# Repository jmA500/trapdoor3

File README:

This project describes a 1.8MB/2MB Trapdoor expansion for the Amiga
500. It includes the Schematics and PCB in the Autodesk Eagle format.

For a detailed description of the project including a comprehensive
Theory of operation, refert to:

https://www.jm27.de/amiga-500-trapdoor-extension/

All the files are licensed under the GPLv2, please mention
jmA500@metweb.de as the original author.

Acknowlegements go to Paradroid at the a1k.org/forum and Individual
Computers for useful suggestions.

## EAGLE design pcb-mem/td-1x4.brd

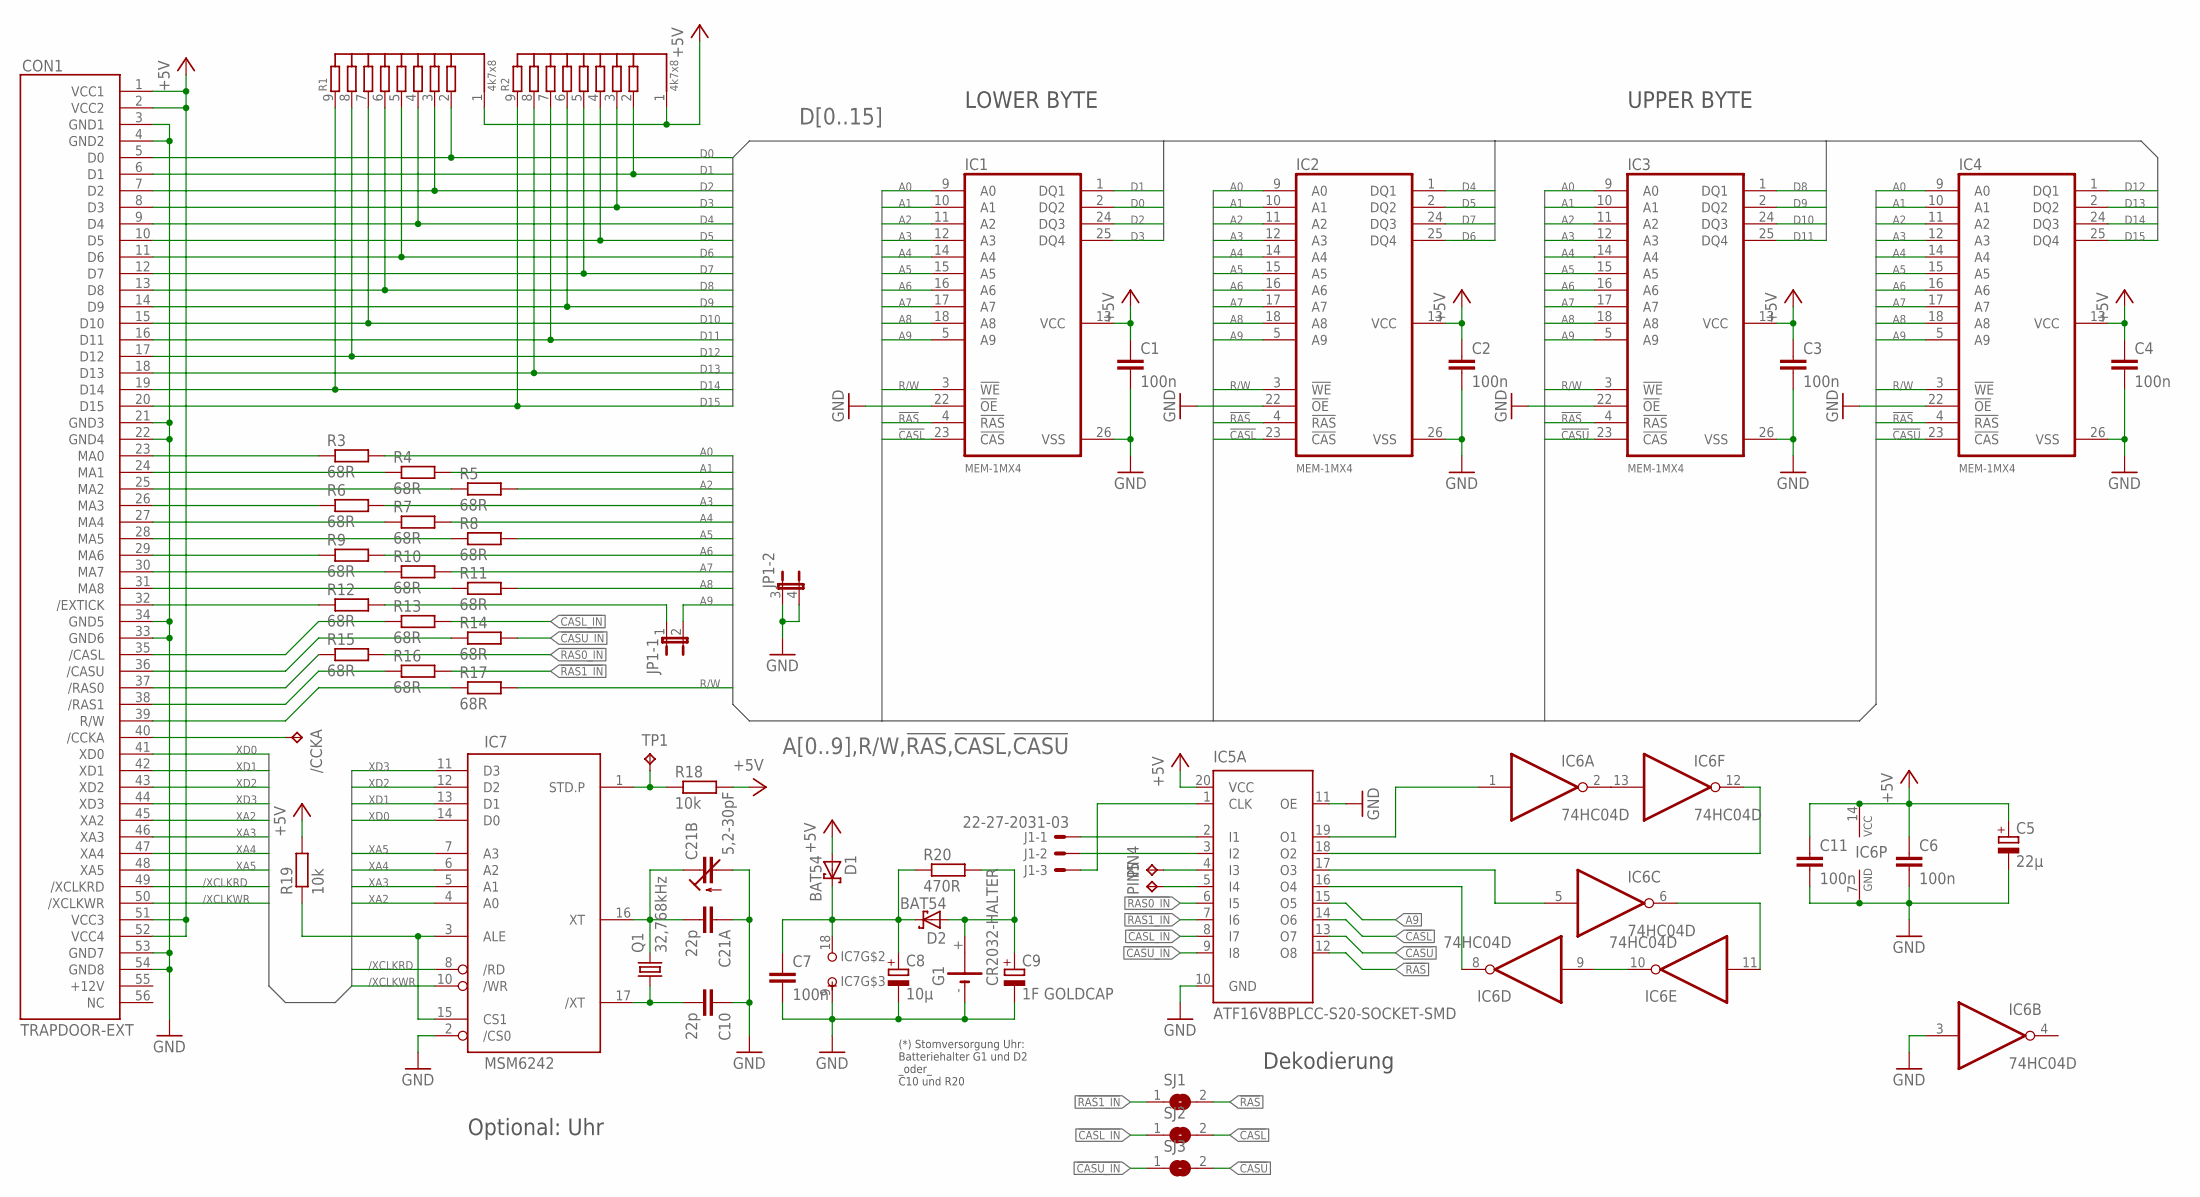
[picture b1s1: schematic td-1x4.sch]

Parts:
/CCKA: PIN2; B1,27
C1, C2, C3, C4, C6, C7, C11: 100n; C0805
C5: 22µ; SMC_C
C8: 10µ; SMC_A
C9: 1F GOLDCAP; GOLDCAP-5
C10, C21A: 22p; C0805
C21B: 5,2-30pF; CTRIM3050.504
CON1: TRAPDOOR-EXT; 2X28/90
D1, D2: BAT54; SOT23
G1: CR2032-HALTER; HALTER2032
IC1, IC2, IC3, IC4: MEM-1MX4; SOJ26-20
IC5A: ATF16V8BPLCC-S20-SOCKET-SMD; PLCC-S20-SOCKET-SMD
IC6: 74HC04D; SO14
IC7: MSM6242; DIL18
J1: 22-27-2031-03; 6410-03
JP1: JP2QE; JP2Q
PIN4: PIN4; B1,27
PIN5: PIN5; B1,27
Q1: 32,768kHz; TC26V
R1, R2: 4k7x8; RN-9
R3, R4, R5, R6, R7, R8, R9, R10, R11, R12, R13, R14, R15, R16, R17: 68R; R0805
R18, R19: 10k; R0805
R20: 470R; R0805
SJ1, SJ2, SJ3: SJ
TP1: TPB1,27; B1,27

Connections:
!CASL: IC1.23 (!CAS), IC2.23 (!CAS), IC5A.14 (O6), SJ2.2
!CASL_IN: IC5A.8 (I7), R13.2, SJ2.1
!CASU: IC3.23 (!CAS), IC4.23 (!CAS), IC5A.13 (O7), SJ3.2
!CASU_IN: IC5A.9 (I8), R14.2, SJ3.1
!EXRAM: CON1.32 (/EXTICK), R12.1
!RAS: IC1.4 (!RAS), IC2.4 (!RAS), IC3.4 (!RAS), IC4.4 (!RAS), IC5A.12 (O8), SJ1.2
!RAS0_IN: IC5A.6 (I5), R15.2
!RAS1_IN: IC5A.7 (I6), R16.2, SJ1.1
+5V: C1.1, C2.1, C3.1, C4.1, C5.+, C6.1, C11.1, CON1.1 (VCC1), CON1.2 (VCC2), CON1.51 (VCC3), CON1.52 (VCC4), D1.1 (A), IC1.13 (VCC), IC2.13 (VCC), IC3.13 (VCC), IC4.13 (VCC), IC5A.20 (VCC), IC6.14 (VCC), R1.1, R2.1, R18.2, R19.2
/XCLKRD: CON1.49 (/XCLKRD), IC7.8 (/RD)
/XCLKWR: CON1.50 (/XCLKWR), IC7.10 (/WR)
A0: IC1.9 (A0), IC2.9 (A0), IC3.9 (A0), IC4.9 (A0), R3.2
A1: IC1.10 (A1), IC2.10 (A1), IC3.10 (A1), IC4.10 (A1), R4.2
A2: IC1.11 (A2), IC2.11 (A2), IC3.11 (A2), IC4.11 (A2), R5.2
A3: IC1.12 (A3), IC2.12 (A3), IC3.12 (A3), IC4.12 (A3), R6.2
A4: IC1.14 (A4), IC2.14 (A4), IC3.14 (A4), IC4.14 (A4), R7.2
A5: IC1.15 (A5), IC2.15 (A5), IC3.15 (A5), IC4.15 (A5), R8.2
A6: IC1.16 (A6), IC2.16 (A6), IC3.16 (A6), IC4.16 (A6), R9.2
A7: IC1.17 (A7), IC2.17 (A7), IC3.17 (A7), IC4.17 (A7), R10.2
A8: IC1.18 (A8), IC2.18 (A8), IC3.18 (A8), IC4.18 (A8), R11.2
A9: IC1.5 (A9), IC2.5 (A9), IC3.5 (A9), IC4.5 (A9), IC5A.15 (O5), JP1.2
D0: CON1.5 (D0), IC1.2 (DQ2), R1.2
D1: CON1.6 (D1), IC1.1 (DQ1), R2.2
D2: CON1.7 (D2), IC1.24 (DQ3), R1.3
D3: CON1.8 (D3), IC1.25 (DQ4), R2.3
D4: CON1.9 (D4), IC2.1 (DQ1), R1.4
D5: CON1.10 (D5), IC2.2 (DQ2), R2.4
D6: CON1.11 (D6), IC2.25 (DQ4), R1.5
D7: CON1.12 (D7), IC2.24 (DQ3), R2.5
D8: CON1.13 (D8), IC3.1 (DQ1), R1.6
D9: CON1.14 (D9), IC3.2 (DQ2), R2.6
D10: CON1.15 (D10), IC3.24 (DQ3), R1.7
D11: CON1.16 (D11), IC3.25 (DQ4), R2.7
D12: CON1.17 (D12), IC4.1 (DQ1), R1.8
D13: CON1.18 (D13), IC4.2 (DQ2), R2.8
D14: CON1.19 (D14), IC4.24 (DQ3), R1.9
D15: CON1.20 (D15), IC4.25 (DQ4), R2.9
GND: C1.2, C2.2, C3.2, C4.2, C5.-, C6.2, C7.2, C8.-, C9.-, C10.1, C11.2, C21A.1, C21B.2 (A), CON1.3 (GND1), CON1.4 (GND2), CON1.21 (GND3), CON1.22 (GND4), CON1.33 (GND6), CON1.34 (GND5), CON1.53 (GND7), CON1.54 (GND8), G1.-, IC1.22 (!OE), IC1.26 (VSS), IC2.22 (!OE), IC2.26 (VSS), IC3.22 (!OE), IC3.26 (VSS), IC4.22 (!OE), IC4.26 (VSS), IC5A.10 (GND), IC5A.11 (OE), IC6.3 (I), IC6.7 (GND), IC7.2 (/CS0), IC7.9 (-UB), JP1.3 (1), JP1.4 (2)
unnamed: CON1.23 (MA0), R3.1
unnamed: CON1.24 (MA1), R4.1
unnamed: CON1.25 (MA2), R5.1
unnamed: CON1.26 (MA3), R6.1
unnamed: CON1.28 (MA5), R8.1
unnamed: CON1.27 (MA4), R7.1
unnamed: CON1.38 (/RAS1), R16.1
unnamed: CON1.29 (MA6), R9.1
unnamed: CON1.30 (MA7), R10.1
unnamed: CON1.31 (MA8), R11.1
unnamed: CON1.35 (/CASL), R13.1
unnamed: CON1.36 (/CASU), R14.1
unnamed: IC5A.18 (O2), IC6.12 (O)
unnamed: CON1.39 (R/W), R17.1
unnamed: C21A.2, C21B.1 (E), IC7.16 (XT), Q1.2
unnamed: C10.2, IC7.17 (/XT), Q1.1
unnamed: IC7.3 (ALE), IC7.15 (CS1), R19.1
unnamed: IC5A.3 (I2), J1.2
unnamed: IC7.1 (STD.P), R18.1, TP1.TP
unnamed: C9.+, D2.1 (A), G1.+, R20.2
unnamed: C7.1, C8.+, D1.3 (C), D2.3 (C), IC7.18 (+UB), R20.1
unnamed: IC5A.4 (I3), PIN4.TP
unnamed: IC5A.5 (I4), PIN5.TP
unnamed: IC6.9 (I), IC6.10 (O)
unnamed: IC5A.16 (O4), IC6.8 (O)
unnamed: IC5A.17 (O3), IC6.5 (I)
unnamed: CON1.37 (/RAS0), R15.1
unnamed: IC6.2 (O), IC6.13 (I)
unnamed: IC5A.19 (O1), IC6.1 (I)
unnamed: IC5A.1 (CLK), J1.3
unnamed: IC6.6 (O), IC6.11 (I)
unnamed: IC5A.2 (I1), J1.1
unnamed: /CCKA.TP, CON1.40 (/CCKA)
unnamed: JP1.1, R12.2
R/W: IC1.3 (!WE), IC2.3 (!WE), IC3.3 (!WE), IC4.3 (!WE), R17.2
XA2: CON1.45 (XA2), IC7.4 (A0)
XA3: CON1.46 (XA3), IC7.5 (A1)
XA4: CON1.47 (XA4), IC7.6 (A2)
XA5: CON1.48 (XA5), IC7.7 (A3)
XD0: CON1.41 (XD0), IC7.14 (D0)
XD1: CON1.42 (XD1), IC7.13 (D1)
XD2: CON1.43 (XD2), IC7.12 (D2)
XD3: CON1.44 (XD3), IC7.11 (D3)

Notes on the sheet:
LOWER BYTE
UPPER BYTE
Optional: Uhr
Dekodierung
(*) Stomversorgung Uhr: Batteriehalter G1 und D2 _oder_ C10 und R20

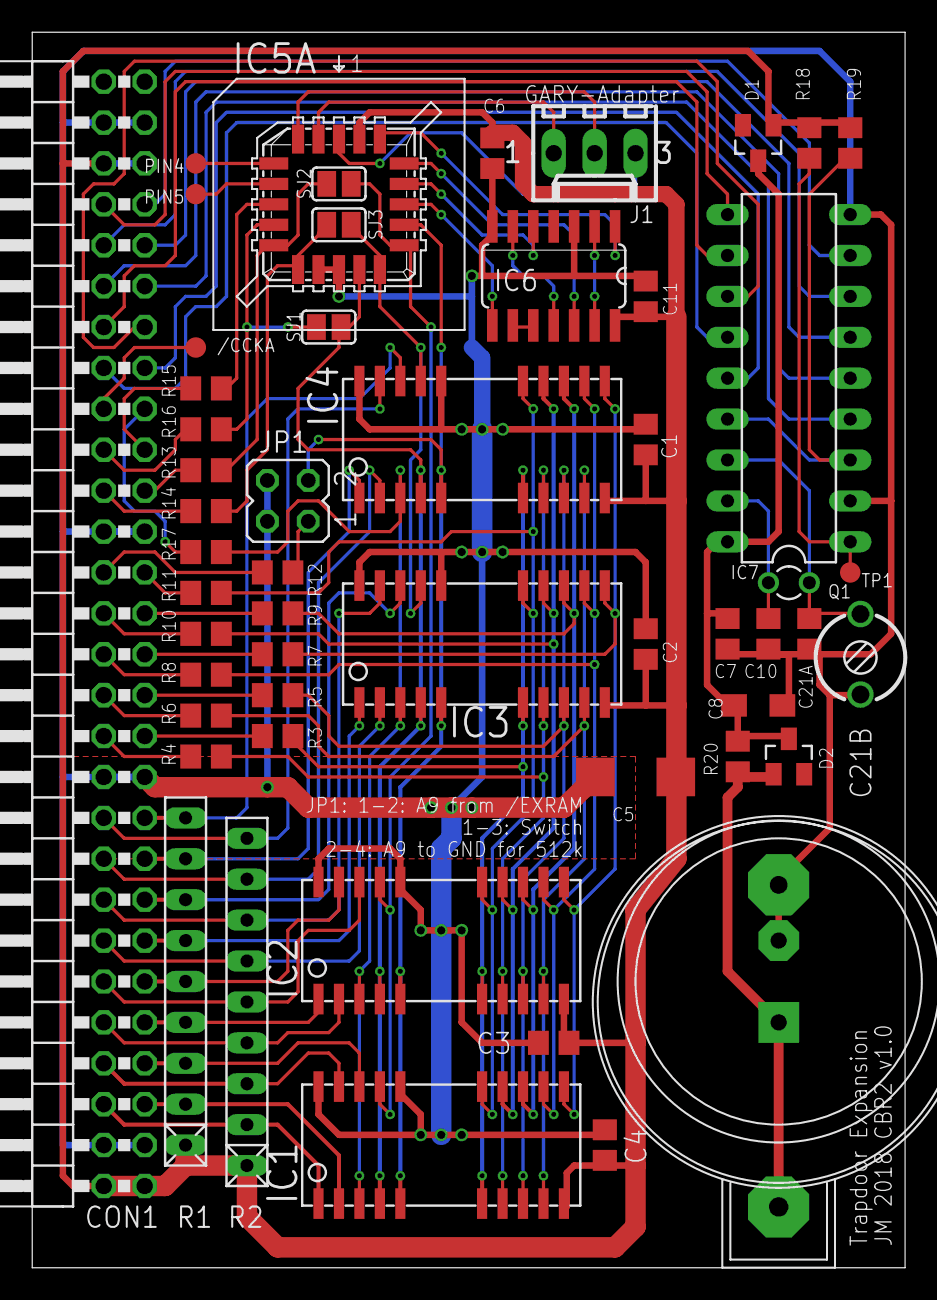
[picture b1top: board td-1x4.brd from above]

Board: 2 copper layers, 54.2 x 76.7 mm, 54 parts (0 on the bottom side), 81 nets.

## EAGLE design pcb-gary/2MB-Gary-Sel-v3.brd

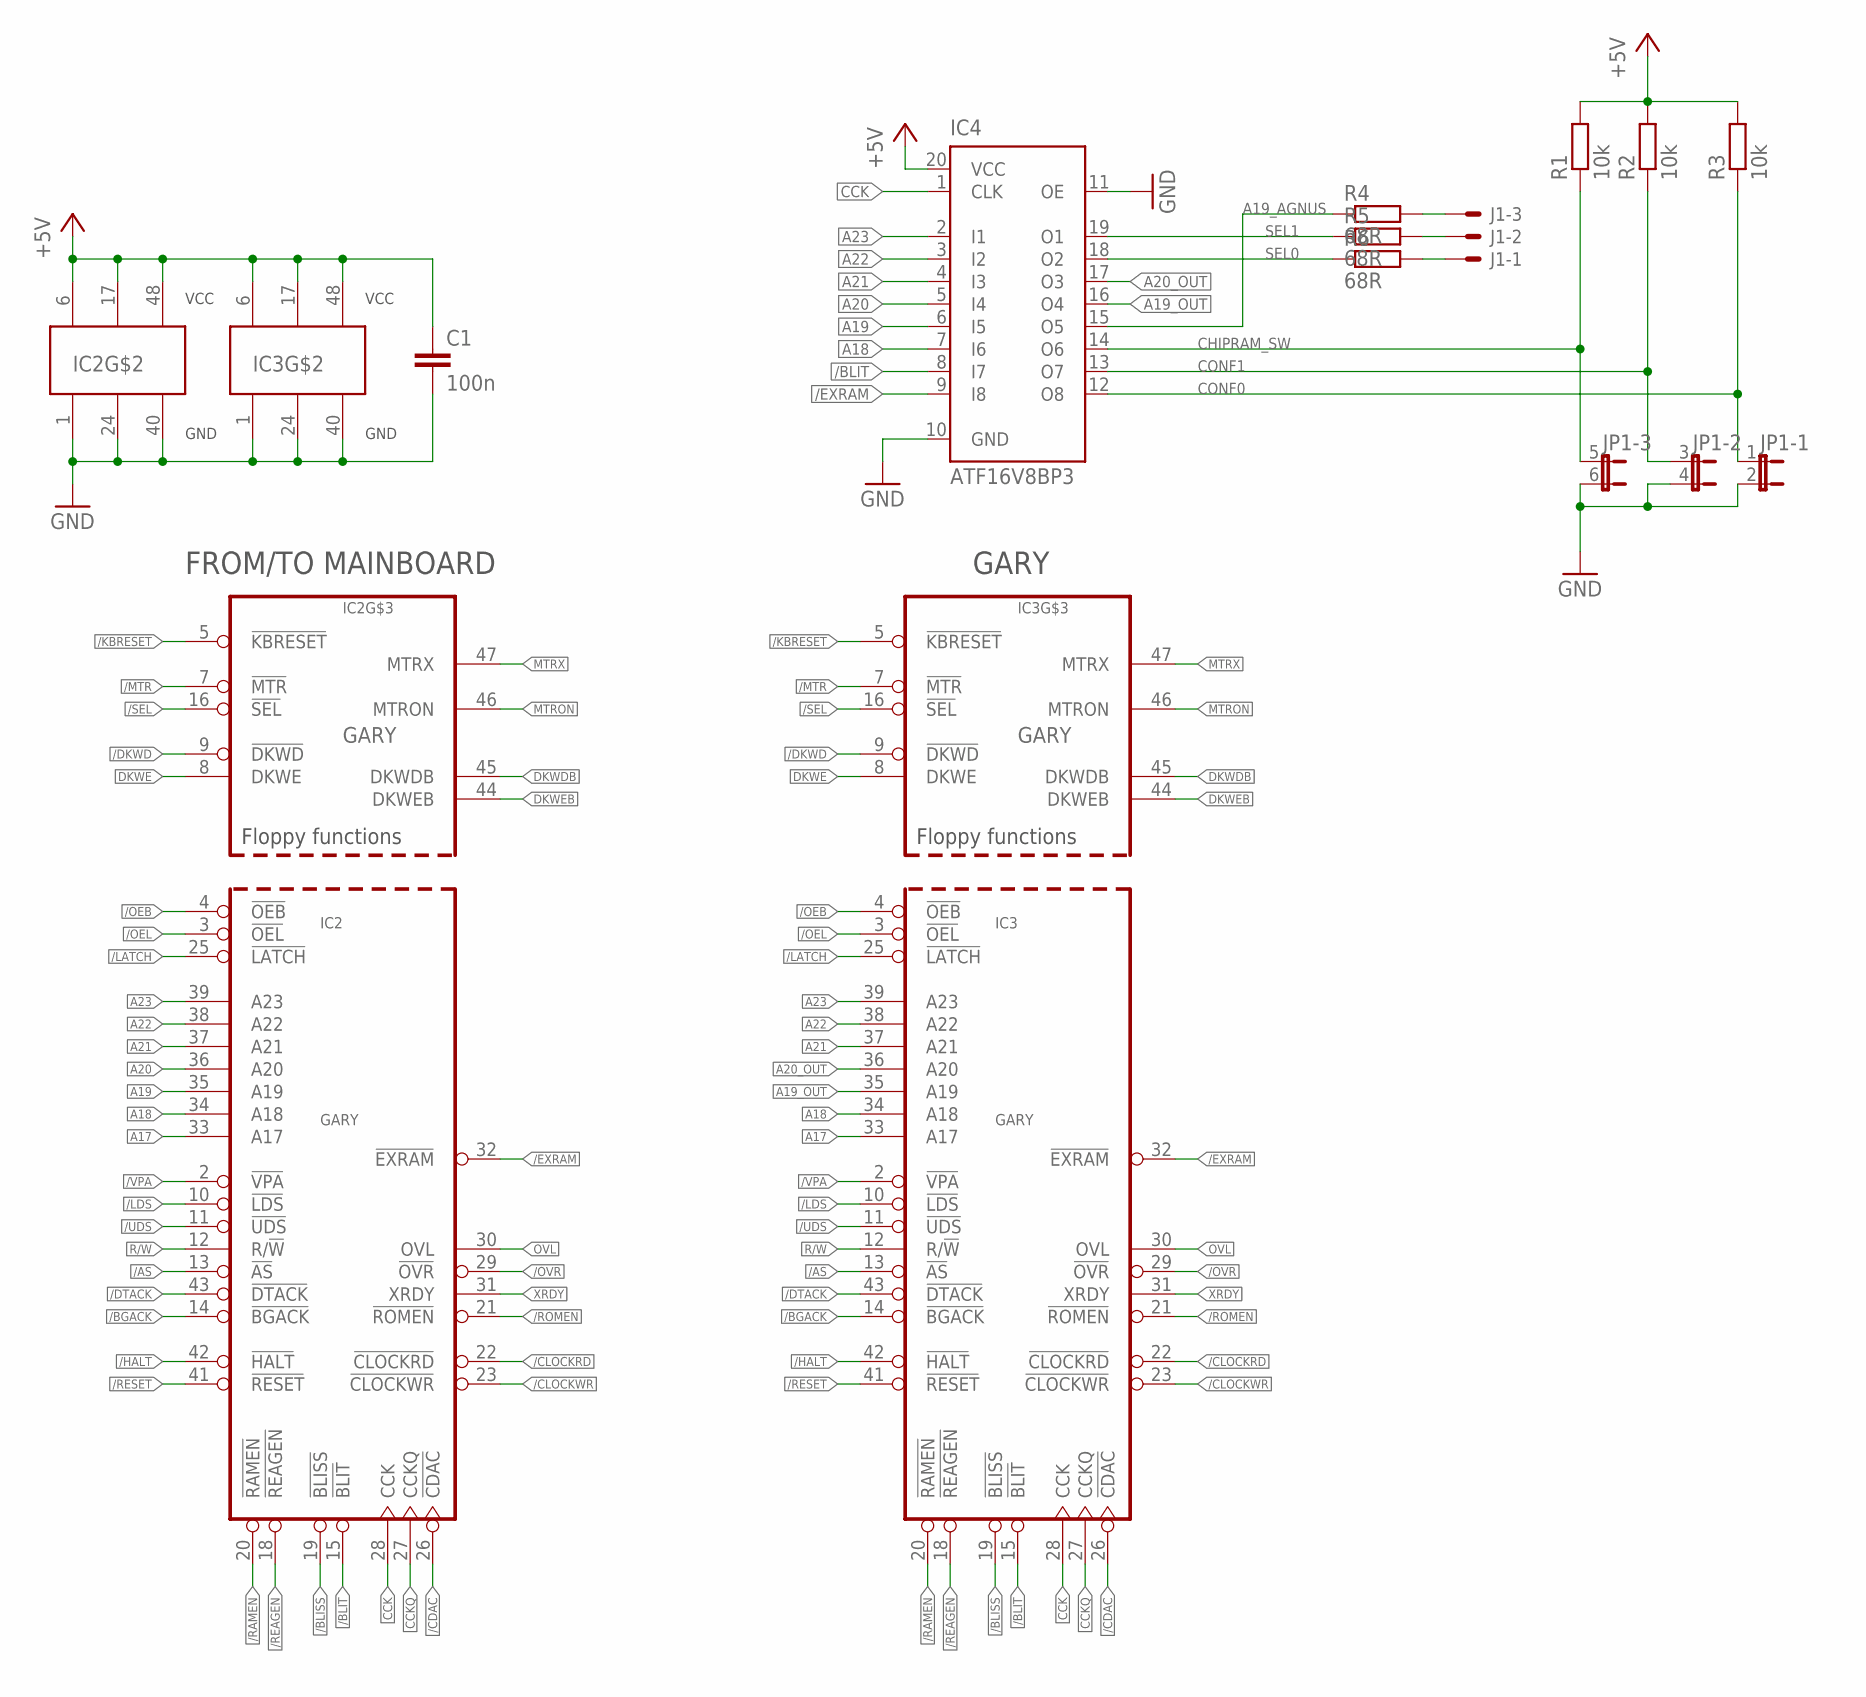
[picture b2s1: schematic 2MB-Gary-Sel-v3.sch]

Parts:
C1: 100n; C0805
IC2: GARY_SOCKET; DIP48-6NOPLACE
IC3: GARY; DIP48-6
IC4: ATF16V8BP3; DIL20
J1: 22-05-7038-03; 7395-03
JP1: JP3QE; JP3Q
R1, R2, R3: 10k; R0805
R4, R5, R6: 68R; R0805

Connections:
+5V: C1.1, IC2.6 (VCC), IC2.17 (VCC), IC2.48 (VCC), IC3.6 (VCC), IC3.17 (VCC), IC3.48 (VCC), IC4.20 (VCC), R1.2, R2.2, R3.2
/AS: IC2.13 (!AS), IC3.13 (!AS)
/BGACK: IC2.14 (!BGACK), IC3.14 (!BGACK)
/BLISS: IC2.19 (!BLISS), IC3.19 (!BLISS)
/BLIT: IC2.15 (!BLIT), IC3.15 (!BLIT), IC4.8 (I7)
/CDAC: IC2.26 (!CDAC), IC3.26 (!CDAC)
/CLOCKRD: IC2.22 (!CLOCKRD), IC3.22 (!CLOCKRD)
/CLOCKWR: IC2.23 (!CLOCKWR), IC3.23 (!CLOCKWR)
/DKWD: IC2.9 (!DKWD), IC3.9 (!DKWD)
/DTACK: IC2.43 (!DTACK), IC3.43 (!DTACK)
/EXRAM: IC2.32 (!EXRAM), IC3.32 (!EXRAM), IC4.9 (I8)
/HALT: IC2.42 (!HALT), IC3.42 (!HALT)
/KBRESET: IC2.5 (!KBRESET), IC3.5 (!KBRESET)
/LATCH: IC2.25 (!LATCH), IC3.25 (!LATCH)
/LDS: IC2.10 (!LDS), IC3.10 (!LDS)
/MTR: IC2.7 (!MTR), IC3.7 (!MTR)
/OEB: IC2.4 (!OEB), IC3.4 (!OEB)
/OEL: IC2.3 (!OEL), IC3.3 (!OEL)
/OVR: IC2.29 (!OVR), IC3.29 (!OVR)
/RAMEN: IC2.20 (!RAMEN), IC3.20 (!RAMEN)
/REAGEN: IC2.18 (!REAGEN), IC3.18 (!REAGEN)
/RESET: IC2.41 (!RESET), IC3.41 (!RESET)
/ROMEN: IC2.21 (!ROMEN), IC3.21 (!ROMEN)
/SEL: IC2.16 (!SEL), IC3.16 (!SEL)
/UDS: IC2.11 (!UDS), IC3.11 (!UDS)
/VPA: IC2.2 (!VPA), IC3.2 (!VPA)
A17: IC2.33 (A17), IC3.33 (A17)
A18: IC2.34 (A18), IC3.34 (A18), IC4.7 (I6)
A19: IC2.35 (A19), IC4.6 (I5)
A19_AGNUS: IC4.15 (O5), R4.1
A19_OUT: IC3.35 (A19), IC4.16 (O4)
A20: IC2.36 (A20), IC4.5 (I4)
A20_OUT: IC3.36 (A20), IC4.17 (O3)
A21: IC2.37 (A21), IC3.37 (A21), IC4.4 (I3)
A22: IC2.38 (A22), IC3.38 (A22), IC4.3 (I2)
A23: IC2.39 (A23), IC3.39 (A23), IC4.2 (I1)
CCK: IC2.28 (CCK), IC3.28 (CCK), IC4.1 (CLK)
CCKQ: IC2.27 (CCKQ), IC3.27 (CCKQ)
CHIPRAM_SW: IC4.14 (O6), JP1.5 (1), R1.1
CONF0: IC4.12 (O8), JP1.1, R3.1
CONF1: IC4.13 (O7), JP1.3 (1), R2.1
DKWDB: IC2.45 (DKWDB), IC3.45 (DKWDB)
DKWE: IC2.8 (DKWE), IC3.8 (DKWE)
DKWEB: IC2.44 (DKWEB), IC3.44 (DKWEB)
GND: C1.2, IC2.1 (GND), IC2.24 (GND), IC2.40 (GND), IC3.1 (GND), IC3.24 (GND), IC3.40 (GND), IC4.10 (GND), IC4.11 (OE), JP1.2, JP1.4 (2), JP1.6 (2)
MTRON: IC2.46 (MTRON), IC3.46 (MTRON)
MTRX: IC2.47 (MTRX), IC3.47 (MTRX)
unnamed: J1.2, R5.2
unnamed: J1.1, R6.2
unnamed: J1.3, R4.2
OVL: IC2.30 (OVL), IC3.30 (OVL)
R/W: IC2.12 (R/!W!), IC3.12 (R/!W!)
SEL0: IC4.18 (O2), R6.1
SEL1: IC4.19 (O1), R5.1
XRDY: IC2.31 (XRDY), IC3.31 (XRDY)

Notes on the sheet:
FROM/TO MAINBOARD
GARY

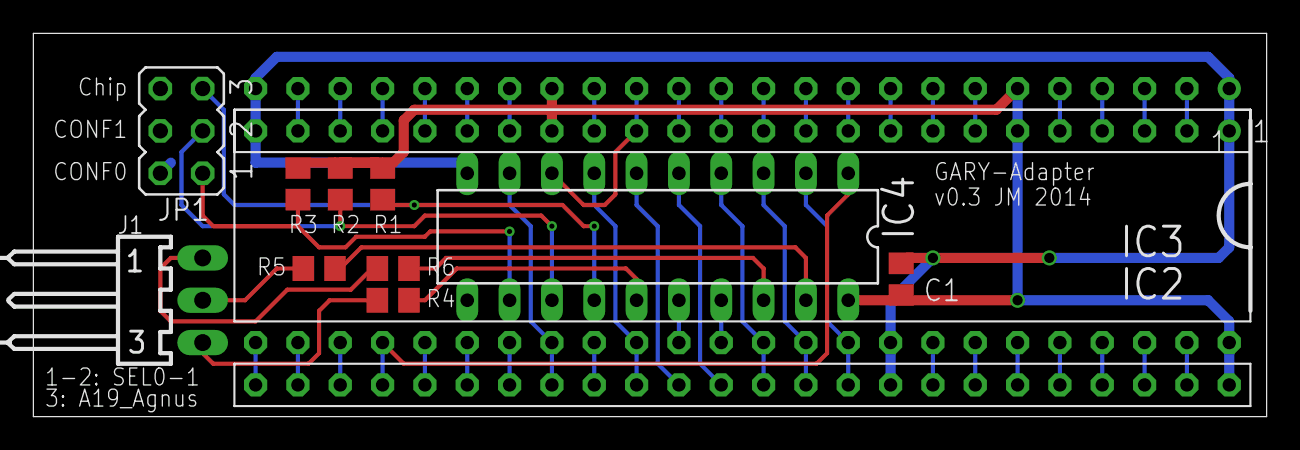
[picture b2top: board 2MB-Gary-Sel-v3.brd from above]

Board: 2 copper layers, 74.0 x 23.0 mm, 12 parts (0 on the bottom side), 55 nets.

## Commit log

2020-02-16 Initial commit.
2020-02-16 Preparing upload to GitHub
2020-02-16 Renamed README to README.md
